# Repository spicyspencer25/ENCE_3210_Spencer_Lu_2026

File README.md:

# ENCE_3210_Spencer_Lu_2026

Hello world

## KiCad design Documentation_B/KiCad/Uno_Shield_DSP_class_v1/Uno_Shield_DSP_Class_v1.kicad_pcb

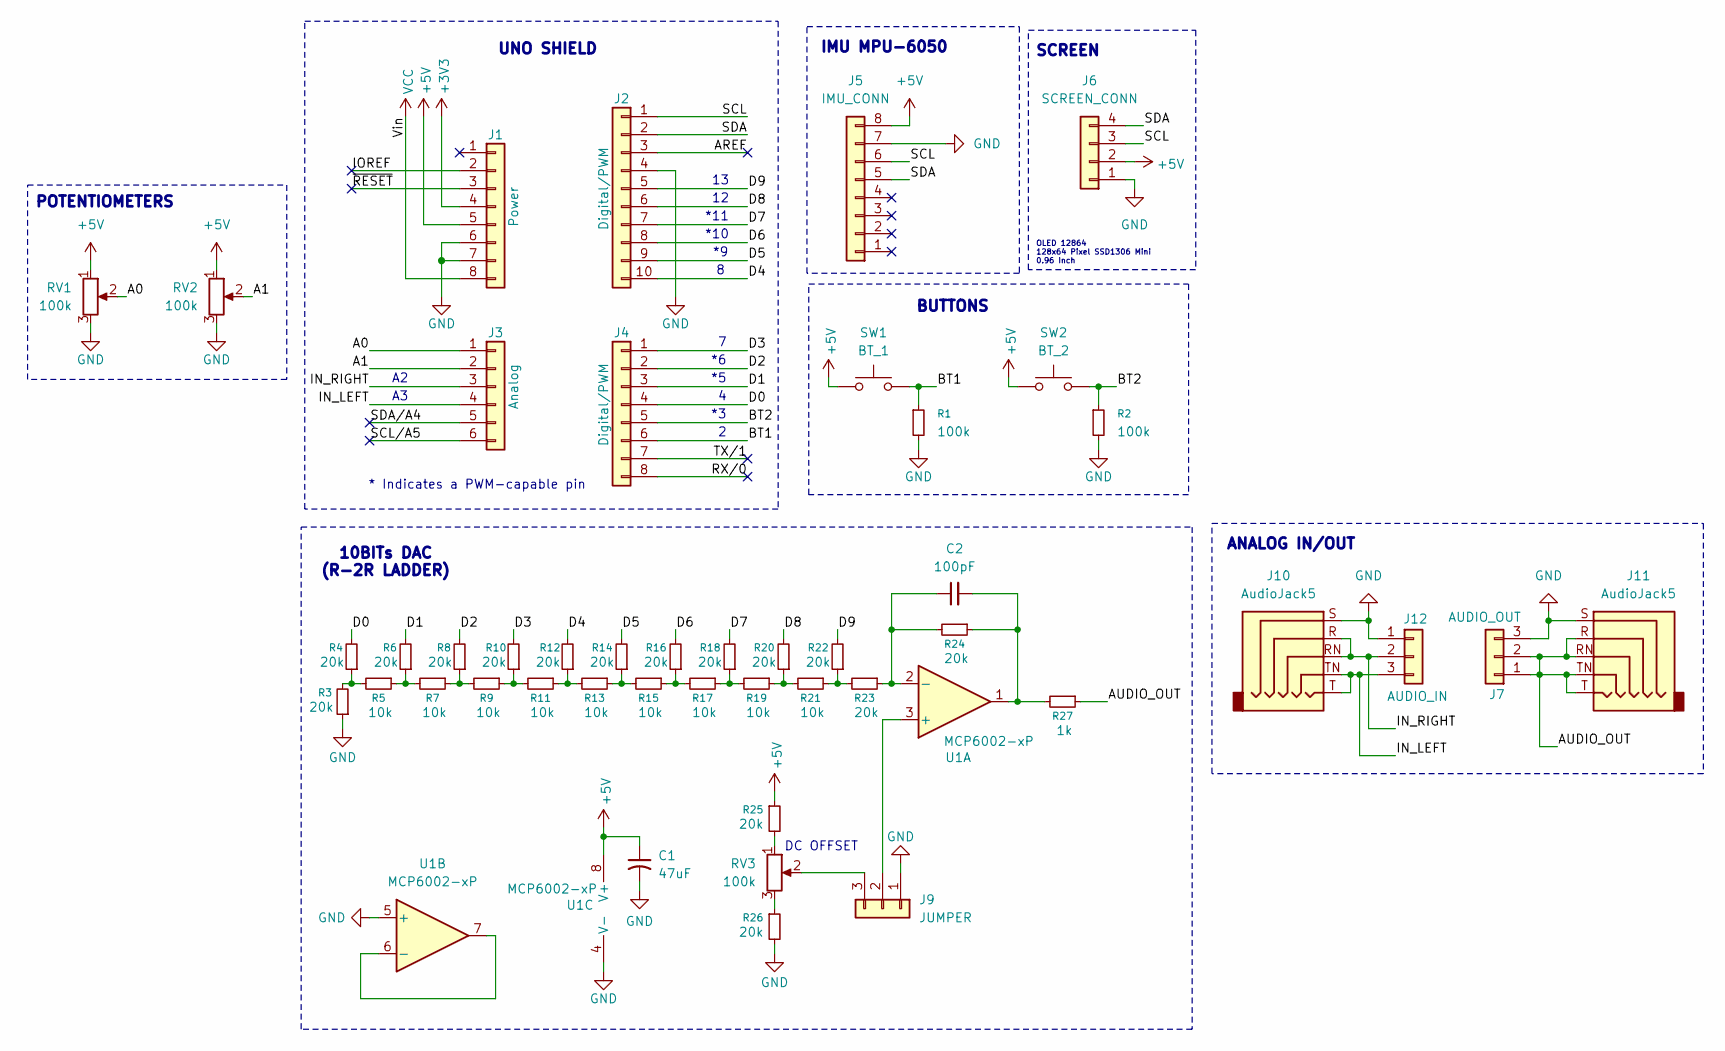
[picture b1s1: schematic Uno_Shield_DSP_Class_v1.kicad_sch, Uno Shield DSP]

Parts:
C1: 47uF; CP_Radial_D8.0mm_P2.50mm
C2: 100pF; C_Disc_D5.0mm_W2.5mm_P2.50mm
J1: Power; PinSocket_1x08_P2.54mm_Vertical
J2: Digital/PWM; PinSocket_1x10_P2.54mm_Vertical
J3: Analog; PinSocket_1x06_P2.54mm_Vertical
J4: Digital/PWM; PinSocket_1x08_P2.54mm_Vertical
J5: IMU_CONN; PinSocket_1x08_P2.54mm_Vertical
J6: SCREEN_CONN; PinHeader_1x04_P2.54mm_Vertical
J7: AUDIO_OUT; PinHeader_1x03_P2.54mm_Vertical
J9: JUMPER; PinHeader_1x03_P2.54mm_Vertical
J10, J11: AudioJack5; Jack_3.5mm_CUI_SJ1-3525N_Horizontal
J12: AUDIO_IN; PinHeader_1x03_P2.54mm_Vertical
R1, R2: 100k; R_Axial_DIN0309_L9.0mm_D3.2mm_P2.54mm_Vertical
R3, R4, R6, R8, R10, R12, R14, R16, R18, R20, R22, R23, R24, R25, R26: 20k; R_Axial_DIN0309_L9.0mm_D3.2mm_P2.54mm_Vertical
R5, R7, R9, R11, R13, R15, R17, R19, R21: 10k; R_Axial_DIN0309_L9.0mm_D3.2mm_P2.54mm_Vertical
R27: 1k; R_Axial_DIN0309_L9.0mm_D3.2mm_P2.54mm_Vertical
RV1, RV2, RV3: 100k; Potentiometer_Bourns_3386P_Vertical
SW1: BT_1; SW_PUSH_6mm
SW2: BT_2; SW_PUSH_6mm
U1: MCP6002-xP; DIP-8_W7.62mm_Socket_LongPads

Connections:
+3V3: J1.4
+5V: C1.1, J1.5, J5.8, J6.2, R25.1, RV1.1, RV2.1, SW1.1, SW2.1, U1.8 (V+)
/A0: J3.1, RV1.2
/A1: J3.2, RV2.2
/AREF: J2.3
/AUDIO_OUT: J7.1, J7.2, J11.R, J11.RN, J11.T, J11.TN, R27.1
/BT1: J4.6, R1.1, SW1.2
/BT2: J4.5, R2.1, SW2.2
/D0: J4.4, R4.2
/D1: J4.3, R6.2
/D2: J4.2, R8.2
/D3: J4.1, R10.2
/D4: J2.10, R12.2
/D5: J2.9, R14.2
/D6: J2.8, R16.2
/D7: J2.7, R18.2
/D8: J2.6, R20.2
/D9: J2.5, R22.2
/IN_LEFT: J3.4, J10.T, J10.TN, J12.3
/IN_RIGHT: J3.3, J10.R, J10.RN, J12.2
/IOREF: J1.2
/RX/0: J4.8
/SCL: J2.1, J5.6, J6.3
/SCL/A5: J3.6
/SDA: J2.2, J5.5, J6.4
/SDA/A4: J3.5
/TX/1: J4.7
/~RESET: J1.3
GND: C1.2, J1.6, J1.7, J2.4, J5.7, J6.1, J7.3, J9.1, J10.S, J11.S, J12.1, R1.2, R2.2, R3.1, R26.2, RV1.3, RV2.3, U1.4 (V-), U1.5 (+)
unnamed: C2.2, R24.1, R27.2, U1.1
unnamed: J9.2, U1.3 (+)
unnamed: J9.3, RV3.2
unnamed: R3.2, R4.1, R5.2
unnamed: R5.1, R6.1, R7.2
unnamed: R7.1, R8.1, R9.2
unnamed: R9.1, R10.1, R11.2
unnamed: R11.1, R12.1, R13.2
unnamed: R13.1, R14.1, R15.2
unnamed: R15.1, R16.1, R17.2
unnamed: R17.1, R18.1, R19.2
unnamed: R19.1, R20.1, R21.2
unnamed: R21.1, R22.1, R23.2
unnamed: R25.2, RV3.1
unnamed: R26.1, RV3.3
unnamed: C2.1, R23.1, R24.2, U1.2 (-)
unnamed: U1.6 (-), U1.7
VCC: J1.8

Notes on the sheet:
BUTTONS
IMU MPU-6050
POTENTIOMETERS
*11
DC OFFSET
10BITs DAC (R-2R LADDER)
ANALOG IN/OUT
*10
OLED 12864 128x64 Pixel SSD1306 Mini 0.96 Inch
* Indicates a PWM-capable pin
SCREEN
UNO SHIELD

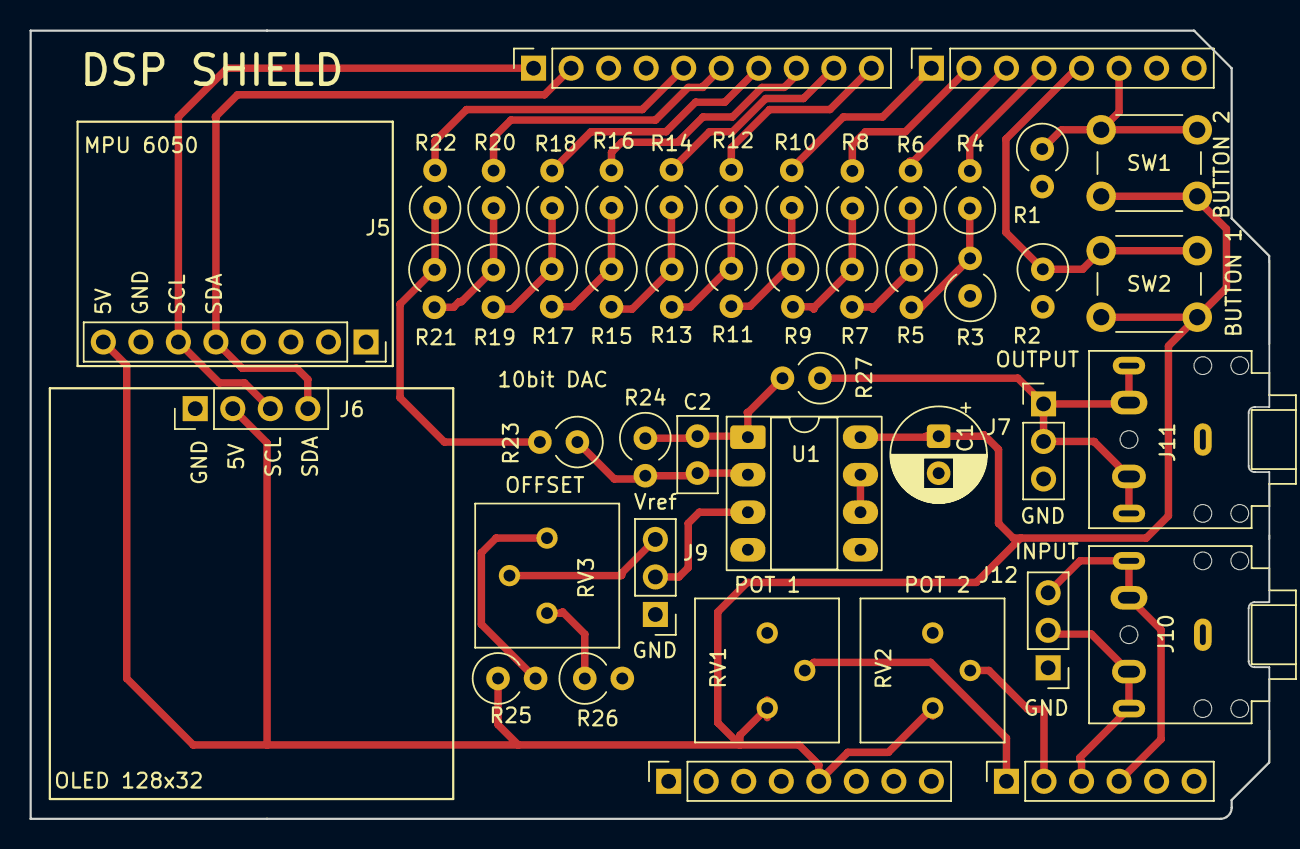
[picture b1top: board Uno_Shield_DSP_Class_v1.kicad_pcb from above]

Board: 2 copper layers, 83.8 x 53.3 mm, 46 parts (0 on the bottom side), 38 nets.

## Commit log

2026-01-16 Add greeting to README
2026-01-30 Add waveformCode for DAC and square wave generation
    This file contains a scope test for the Phase B prototype, detailing the setup and usage of a 10-bit R-2R DAC data bus, along with a square wave output for testing.
2026-01-30 Add files via upload
    slight correction in timer2
2026-02-02 Add initial content to readMe.md for Lab 1
2026-02-09 Add DAC prototype code with ramp and square wave output
    This code implements a 10-bit R-2R DAC that outputs a ramp waveform and a 1 kHz square wave for testing.
2026-02-27 Add initial README for lab 4
2026-03-03 Create Introduction
2026-03-03 Create Design Stage
2026-03-03 Create Prototype Stage
2026-03-03 Create PCB Design
2026-03-03 Create Assemble Stage
2026-03-03 Create Testing Stage
2026-03-09 Add initial content to readMe.md
2026-03-16 Create BOM
2026-03-16 Add files via upload
    updated document
2026-03-16 Update readMe.md with project file details
